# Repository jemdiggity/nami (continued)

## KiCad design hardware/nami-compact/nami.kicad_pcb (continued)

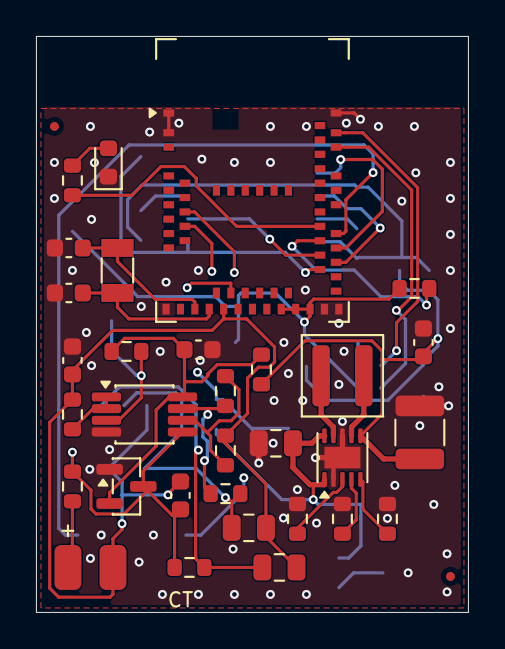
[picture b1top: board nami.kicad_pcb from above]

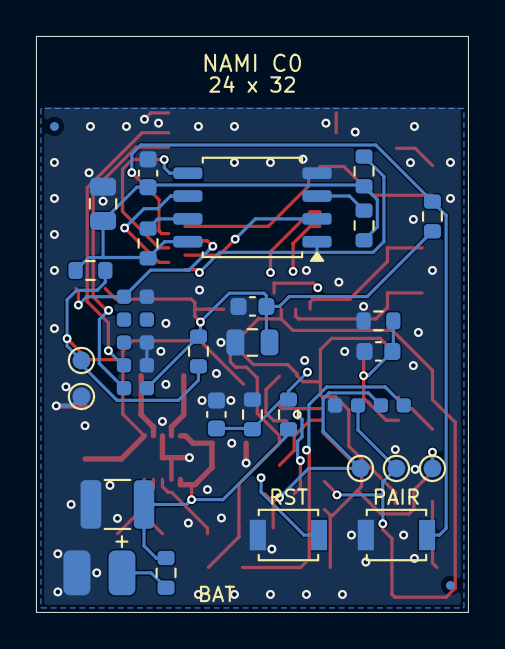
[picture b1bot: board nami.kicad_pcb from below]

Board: 4 copper layers, 24.0 x 32.0 mm, 63 parts (30 on the bottom side), 36 nets.

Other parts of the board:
FID1, FID2, FID3, FID4: Fiducial_0.5mm_Mask1mm

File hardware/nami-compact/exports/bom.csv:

Reference,Value,MPN,Footprint,DNP,Note
J2,BATTERY / BENCH 2.0-3.3V,,Nami:WirePads_2_P2.5,False,Bare solder pads; external strain relief required; no purchased connector
R1,0R / AMMETER,,Resistor_SMD:R_0603_1608Metric,False,Remove to insert current meter; never attach two supplies
C1,100u 6.3V X5R,GRM32ER60J107ME20L,Capacitor_SMD:C_1210_3225Metric,False,Verify effective capacitance and cold-cell startup
C2,10u 10V X7R,,Capacitor_SMD:C_0805_2012Metric,False,
U1,TPS63900DSKR,TPS63900DSKR,Package_SON:WSON-10-1EP_2.5x2.5mm_P0.5mm_EP1.2x2mm,False,
L1,2.2uH >=2A,XAL4020-222MEC,Inductor_SMD:L_Coilcraft_XAL4020-XXX,False,Verify land pattern before procurement
R2,0R,,Resistor_SMD:R_0603_1608Metric,False,
R3,1.87k 1%,,Resistor_SMD:R_0603_1608Metric,False,25mA input-current limit; measure startup and flash load
R4,13.3k 1%,,Resistor_SMD:R_0603_1608Metric,False,SEL=0 selects 3.0V
C3,47u 6.3V X5R,,Capacitor_SMD:C_1210_3225Metric,False,
C4,100n 10V X7R,,Capacitor_SMD:C_0603_1608Metric,False,
R5,0R / CURRENT LINK,,Resistor_SMD:R_0603_1608Metric,False,
R6,0R / CURRENT LINK,,Resistor_SMD:R_0603_1608Metric,False,
R7,0R / CURRENT LINK,,Resistor_SMD:R_0603_1608Metric,False,
TP1,VREG,,TestPoint:TestPoint_Pad_D1.0mm,False,
TP2,GND,,TestPoint:TestPoint_Pad_D1.0mm,False,
J1,CT HARNESS,,Nami:WirePads_2_P2.5,False,Bare solder pads; external strain relief required; no purchased connector
R8,1k,,Resistor_SMD:R_0603_1608Metric,False,
C5,1n C0G,,Capacitor_SMD:C_0603_1608Metric,False,
D1,BAV199,"BAV199,215",Package_TO_SOT_SMD:SOT-23,False,Low-leakage series diode pinout compatible with BAV99; not a mains barrier
R9,1M 0.1%,,Resistor_SMD:R_0603_1608Metric,False,
R10,1M 0.1%,,Resistor_SMD:R_0603_1608Metric,False,
C6,1u X7R,,Capacitor_SMD:C_0603_1608Metric,False,
U2,OPA2333AIDGKR,OPA2333AIDGKR,Package_SO:VSSOP-8_3x3mm_P0.65mm,False,
R11,100R,,Resistor_SMD:R_0603_1608Metric,False,
C7,1u X7R,,Capacitor_SMD:C_0603_1608Metric,False,
R12,10k 0.1%,,Resistor_SMD:R_0603_1608Metric,False,
R13,309k 0.1%,,Resistor_SMD:R_0603_1608Metric,False,Gain 31.9 relative to VMID
R14,1k,,Resistor_SMD:R_0603_1608Metric,False,
C8,22n C0G,,Capacitor_SMD:C_0805_2012Metric,False,
R15,1k,,Resistor_SMD:R_0603_1608Metric,False,
C9,47n C0G,,Capacitor_SMD:C_0805_2012Metric,False,
C10,100n X7R,,Capacitor_SMD:C_0603_1608Metric,False,
TP3,SENSE,,TestPoint:TestPoint_Pad_D1.0mm,False,
TP4,VMID,,TestPoint:TestPoint_Pad_D1.0mm,False,
TP5,ADC_HIGH,,TestPoint:TestPoint_Pad_D1.0mm,False,
U3,MDBT50Q-1MV2,MDBT50Q-1MV2,RF_Module:Raytac_MDBT50Q,False,
C11,10u 10V X7R,,Capacitor_SMD:C_0805_2012Metric,False,
C12,100n X7R,,Capacitor_SMD:C_0603_1608Metric,False,
Y1,32.768kHz CL=7pF,ABS07-32.768KHZ-7-T,Crystal:Crystal_SMD_3215-2Pin_3.2x1.5mm,False,9pF capacitors assume approximately 2.5pF stray; characterize
C13,9p C0G,,Capacitor_SMD:C_0603_1608Metric,False,
C14,9p C0G,,Capacitor_SMD:C_0603_1608Metric,False,
U4,W25Q128JVSIQ,W25Q128JVSIQ,Package_SO:SOIC-8_5.3x5.3mm_P1.27mm,False,
R16,100k,,Resistor_SMD:R_0603_1608Metric,False,
R17,100k,,Resistor_SMD:R_0603_1608Metric,False,
R18,100k,,Resistor_SMD:R_0603_1608Metric,False,
C15,100n X7R,,Capacitor_SMD:C_0603_1608Metric,False,
C16,10u 10V X7R,,Capacitor_SMD:C_0805_2012Metric,False,
J3,SWD POGO 1.27mm,,Nami:Pogo_2x05_P1.27,False,"Custom fixture pads, ARM pin numbering; VTref sense only; no header"
SW1,PAIR,B3U-1000P,Button_Switch_SMD:SW_SPST_B3U-1000P,False,
R19,100k,,Resistor_SMD:R_0603_1608Metric,False,
SW2,RESET,B3U-1000P,Button_Switch_SMD:SW_SPST_B3U-1000P,False,
R20,100k,,Resistor_SMD:R_0603_1608Metric,False,
R21,4.7k,,Resistor_SMD:R_0603_1608Metric,False,
D2,GREEN,,LED_SMD:LED_0603_1608Metric,False,Normally off
R22,2M 1%,,Resistor_SMD:R_0603_1608Metric,False,
R23,1M 1%,,Resistor_SMD:R_0603_1608Metric,False,
C17,100n X7R,,Capacitor_SMD:C_0603_1608Metric,False,
J4,ANALOG POGO,,Nami:Pogo_1x04_P1.27,False,

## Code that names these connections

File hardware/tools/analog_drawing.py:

"""Conventional wired analog sheet; preserves symbol identities and circuit nets."""
import math
from collections import Counter
import sexpdata as sx
S=sx.Symbol
def field(a,k):return next((v for v in a if isinstance(v,list) and str(v[0])==k),None)
def redraw(doc,uid):
    # Sheet layout is presentation only. The exported netlist verifies equivalence.
    field(doc,'paper')[1]='A3'
    doc[:]=[x for x in doc if not(isinstance(x,list) and str(x[0]) in ['wire','global_label','label','junction','text'])]
    symbols={}
    for a in doc:
        if isinstance(a,list) and str(a[0])=='symbol':
            ref=next(v[2] for v in a if isinstance(v,list) and str(v[0])=='property' and v[1]=='Reference')
            symbols[ref,int(field(a,'unit')[1])]=a
    locations={('J1',1):(30,80,180),('R8',1):(60,80,90),('C5',1):(90,97,0),('D1',1):(120,60,0),
      ('U2',2):(150,82.54,0),('R13',1):(165,112.5,270),('R12',1):(130,130,0),
      ('R14',1):(215,40,90),('C8',1):(240,55,0),('R15',1):(215,82.54,90),('C9',1):(240,100,0),
      ('TP3',1):(80,75,0),('TP5',1):(260,75,0),
      ('R9',1):(50,180,0),('R10',1):(50,207,0),('C6',1):(75,207,0),
      ('U2',1):(120,194.54,0),('R11',1):(165,194.54,90),('C7',1):(185,209,0),('TP4',1):(205,190,0),
      ('U2',3):(260,193,0),('C10',1):(290,193,0)}
    libs={x[1]:x for x in field(doc,'lib_symbols')[1:]};pins={}
    for key,a in symbols.items():
        x,y,angle=locations[key];field(a,'at')[1:]=[x,y,angle]
        ref,unit=key; lib=libs[field(a,'lib_id')[1]]
        for sub in lib:
            if not isinstance(sub,list) or str(sub[0])!='symbol':continue
            if int(sub[1].split('_')[-2]) not in [0,unit]:continue
            for pin in sub:
                if not isinstance(pin,list) or str(pin[0])!='pin':continue
                num=field(pin,'number')[1];px,py=map(float,field(pin,'at')[1:3]);r=math.radians(angle)
                pins[ref,num]=(round(x+px*math.cos(r)-py*math.sin(r),4),round(y-px*math.sin(r)-py*math.cos(r),4))
        for prop in [v for v in a if isinstance(v,list) and str(v[0])=='property']:
            if prop[1] not in ['Reference','Value']:continue
            n=0 if prop[1]=='Reference' else 1
            if ref.startswith(('R','C')) and angle in [90,270]:at=(x,y-5+2.6*n)
            elif ref.startswith(('R','C')):at=(x+8,y-1.3+2.6*n)
            elif ref=='U2' and unit<3:at=(x+2,y-10+2.6*n)
            elif ref=='U2':at=(x+8,y-1.3+2.6*n)
            elif ref=='J1':at=(x,y+8+2.6*n)
            else:at=(x+5,y-6+2.6*n)
            field(prop,'at')[1:]=[*at,90 if angle in [90,270] else 0]
    def pin(ref,n):return pins[ref,str(n)]
    segments=[];labels=[]
    def wire(*pts):segments.extend(zip(pts,pts[1:]))
    def label(net,point,angle=0):
        labels.append(point);doc.append([S('global_label'),net,[S('shape'),S('bidirectional')],[S('at'),*point,angle],[S('effects'),[S('font'),[S('size'),1,1]]],[S('uuid'),uid('analog-label/'+net+str(point))]])
    def stub(ref,num,net,point):wire(pin(ref,num),point);label(net,point)
    def note(t,x,y,size=1.4):doc.append([S('text'),t,[S('at'),x,y,0],[S('effects'),[S('font'),[S('size'),size,size]]],[S('uuid'),uid('analog-note/'+t)]])
    wire(pin('J1',1),(45,80),pin('R8',1));label('CT_P',(45,80));stub('J1',2,'VMID',(40,77.46))
    wire(pin('R8',2),(80,80),(90,80),(100,80),(120,80),pin('U2',5));wire((80,80),pin('TP3',1));label('SENSE',(80,80))
    wire((90,80),pin('C5',1));stub('C5',2,'VMID',(90,108))
    wire((120,80),pin('D1',3));stub('D1',1,'GND',(107,60));stub('D1',2,'VDD_A',(138,60))
    wire((100,80),(100,40),pin('R14',1));wire(pin('R14',2),(240,40),(265,40));label('ADC_LOW',(265,40),180)
    wire((240,40),pin('C8',1));stub('C8',2,'VMID',(240,65))
    wire(pin('U2',7),(185,82.54),pin('R15',1));label('HIGH_OUT',(185,82.54),180)
    wire(pin('R15',2),(240,82.54),(260,82.54),(265,82.54));wire((260,82.54),pin('TP5',1));label('ADC_HIGH',(265,82.54),180)
    wire((240,82.54),pin('C9',1));stub('C9',2,'VMID',(240,112))
    wire((185,82.54),(185,112.5),pin('R13',1));wire(pin('R13',2),(130,112.5),pin('R12',1))
    wire((130,112.5),(130,85.08),pin('U2',6));wire((130,112.5),(122,112.5));label('GAIN_FB',(122,112.5))
    stub('R12',2,'VMID',(130,140))
    stub('R9',1,'VDD_A',(50,167));wire(pin('R9',2),(50,192),pin('R10',1));stub('R10',2,'GND',(50,218))
    wire((50,192),(75,192),(95,192),pin('U2',3));wire((75,192),pin('C6',1));stub('C6',2,'GND',(75,218))
    wire((95,192),(95,184));label('VMID_DIV',(95,184))
    wire(pin('U2',1),(140,194.54),(147,194.54),pin('R11',1))
    wire(pin('U2',2),(100,197.08),(100,215),(140,215),(140,194.54))
    wire((147,194.54),(147,185));label('VMID_BUF',(147,185),180)
    wire(pin('R11',2),(185,194.54),(205,194.54),(220,194.54));label('VMID',(220,194.54),180)
    wire((185,194.54),pin('C7',1));stub('C7',2,'GND',(185,218));wire((205,194.54),pin('TP4',1))
    stub('U2',8,'VDD_A',(257.46,175));stub('U2',4,'GND',(257.46,211))
    stub('C10',1,'VDD_A',(290,175));stub('C10',2,'GND',(290,211))
    note('NAMI / ANALOG FRONT END',190,18,2.5)
    note('CURRENT SIGNAL / NON-INVERTING GAIN = 1 + 309k / 10k = 31.9',160,29,1.4)
    note('MIDPOINT REFERENCE / UNITY-GAIN BUFFER',120,157,1.6)
    note('SUPPLY DECOUPLING',277,160,1.4)
    note('Permanent 5-ohm burden stays at the CT head. J1 return is VMID, not GND.',160,239,1.3)
    note('Both ADC paths measure differentially against VMID. Nominal supply 3.0 V; midpoint 1.5 V.',160,247,1.3)
    # Split at every branch endpoint and add explicit junction dots.
    vertices=set(labels)|{a for a,z in segments}|{z for a,z in segments};edges=set()
    for a,z in segments:
        dx,dy=z[0]-a[0],z[1]-a[1];den=dx*dx+dy*dy
        if not den:continue
        pts=[q for q in vertices if abs((q[0]-a[0])*dy-(q[1]-a[1])*dx)<1e-5 and -1e-6<=((q[0]-a[0])*dx+(q[1]-a[1])*dy)/den<=1+1e-6]
        pts.sort(key=lambda q:((q[0]-a[0])*dx+(q[1]-a[1])*dy)/den)
        for f,t in zip(pts,pts[1:]):edges.add(tuple(sorted([f,t])))
    degree=Counter()
    for a,z in sorted(edges):
        degree[a]+=1;degree[z]+=1
        doc.append([S('wire'),[S('pts'),[S('xy'),*a],[S('xy'),*z]],[S('stroke'),[S('width'),0],[S('type'),S('default')]],[S('uuid'),uid('analog-wire/'+str(a)+str(z))]])
    for point,n in degree.items():
        if n>=3:doc.append([S('junction'),[S('at'),*point],[S('diameter'),0],[S('color'),0,0,0,0],[S('uuid'),uid('analog-junction/'+str(point))]])
    # KiCad's standard 50-mil connection grid. Symbol pin offsets are integral
    # grid units, so snapping origins and explicit wire endpoints preserves nets.
    def snap_tree(a):
        if not isinstance(a,list):return
        if a and str(a[0]) in ['at','xy']:
            a[1]=round(round(float(a[1])/1.27)*1.27,4)
            a[2]=round(round(float(a[2])/1.27)*1.27,4)
        for child in a:snap_tree(child)
    for a in doc:
        if isinstance(a,list) and str(a[0])!='lib_symbols':snap_tree(a)
    return doc
